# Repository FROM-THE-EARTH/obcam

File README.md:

# obcam

`obcam` is the flight camera module and program for the OB team rocket in NSE 2022. See [the site](https://FROM-THE-EARTH.github.io/obcam/) for details.

## Install

After configuration for network connection and installation of `git` and `pip`, run

```bash
python -m pip install git+https://github.com/FROM-THE-EARTH/obcam.git
```

## Install and Activate the flight camera mode

After configuration for network connection and installation of `git`, run

```bash
git clone https://github.com/FROM-THE-EARTH/obcam.git
cd obcam

# After filling out and confirming the glm.py
# See the documentation for detail of the settings.
sudo ./install.sh
```

## Scripts

Scripts in the `scripts` directory may be useful if you want some small operations like installing just `obcam`, activate the flight camera mode, or deactivate the flight camera mode. See [the site](https://FROM-THE-EARTH.github.io/obcam/scripts/) for more information.

**`install.sh`**

This script installs `obcam` and activates the flight camera mode simultaneously.

**`scripts/activate_flightcam.sh`**

This script activates the flight camera mode of the `obcam`. In the flight camera mode, the program of the `obcam` run automatically when booting.

**`scripts/deactivate_flightcam.sh`**

This script deactivates the flight camera mode.

**`scripts/expand_swap.sh`**

This script expands size of the swap file `/var/swap`. In the default setting, size of the swap will be changed to 2048 MB.

**`scripts/install_obcam.sh`**

This script installs the `obcam` module using `pip`. Note that `pip` should be installed before executing this script.

**`scripts/install_pip.sh`**

This script installs `pip`. Note that `pip` could be not installed yet right after the first booting. Thus, this script might be useful in the situation.

**`scripts/uninstall_obcam.sh`**

This script uninstalls the `obcam` module using `pip`.

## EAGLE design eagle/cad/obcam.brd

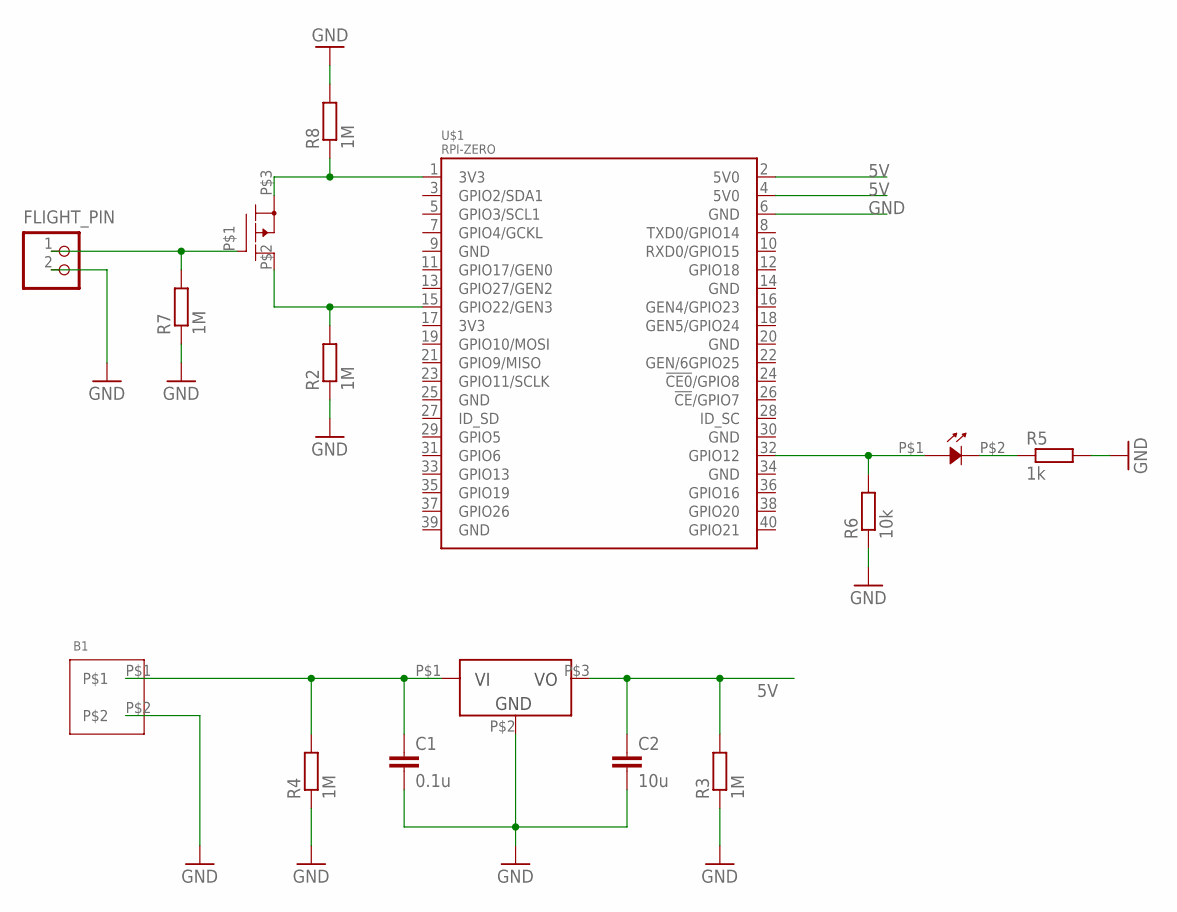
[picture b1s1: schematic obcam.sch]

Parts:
B1: 9V_BATTERY_HOLDER
C1: 0.1u; C2012
C2: 10u; C2012
D1: SML-E1X
FLIGHT_PIN: B2B-XH-A
IC1: NJM2391; TO252
IC2: TJ8S06M3L; TO252
R2, R3, R4, R7, R8: 1M; M2012
R5: 1k; M2012
R6: 10k; M2012
U$1: RPI-ZERO; RASP_PI_ZERO_BOARD_FULL

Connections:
3V3@1: IC2.P$3, R8.1, U$1.1 (3V3)
5V: C2.1, IC1.P$3, R3.2, U$1.2 (5V0), U$1.4 (5V0)
FLIGHT_IO: IC2.P$2, R2.2, U$1.15 (GPIO22/GEN3)
GND: B1.P$2, C1.2, C2.2, FLIGHT_PIN.2, IC1.P$2, R2.1, R3.1, R4.1, R5.2, R6.1, R7.1, R8.2, U$1.6 (GND)
unnamed: B1.P$1, C1.1, IC1.P$1, R4.2
unnamed: FLIGHT_PIN.1, IC2.P$1, R7.2
unnamed: D1.P$2, R5.1
unnamed: D1.P$1, R6.2, U$1.32 (GPIO12)

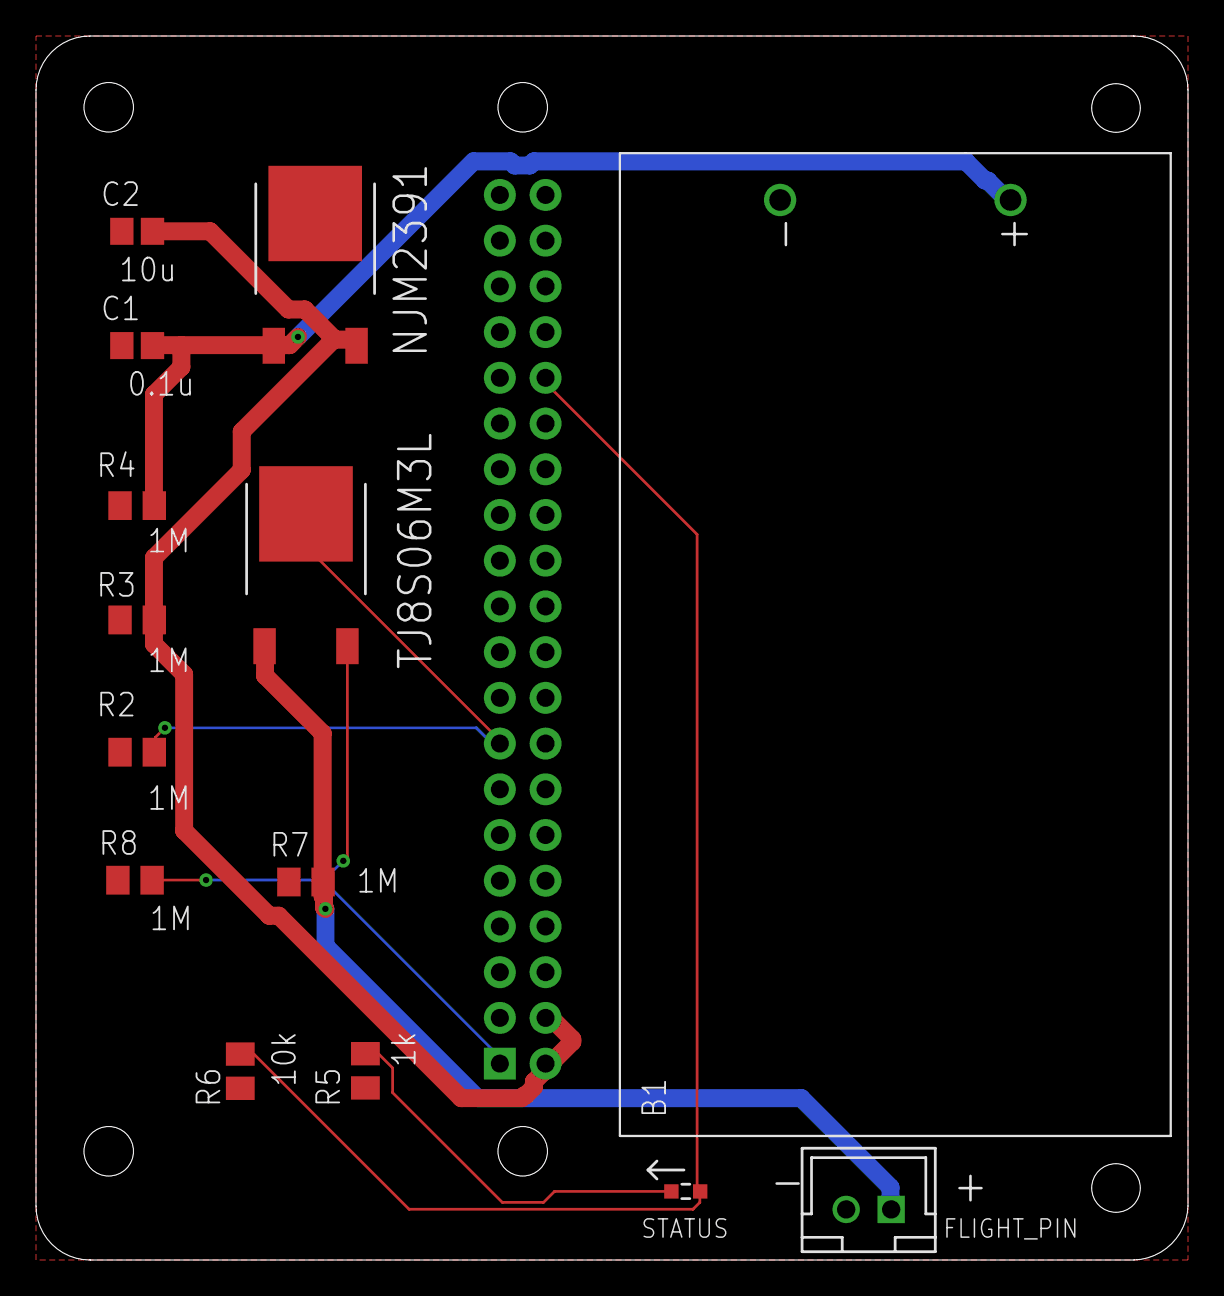
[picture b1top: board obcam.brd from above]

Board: 2 copper layers, 64.0 x 68.0 mm, 15 parts (1 on the bottom side), 8 nets.

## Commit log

2022-07-30 first commit.
2022-07-30 Added installation of `distutils` for `pip`.
2022-07-30 Added small scripts for operation.
2022-07-30 Changed modes of scripts to be executable.
2022-07-30 Added explanation of the scripts.
2022-07-30 Changed the flight pin level logic.
2022-07-30 Took noise measures when detecting a flight pin to be connected.
2022-07-30 Fixed a bug aboout noise measures.
2022-07-30 Added another command for activating camera
2022-07-30 Fixed the library of TJ8S06M3L and updated CAD.
2022-07-30 Removed an useless line for activation of camera
2022-07-31 Added a rule for YAML.
2022-07-31 Added pre-commit settings.
2022-07-31 Fixed the pre-commit settings.
2022-07-31 Wrote the documentation.
2022-07-31 Fixed typos.
2022-07-31 Added an action that updates the site of GitHub pages.
2022-07-31 Updated package dependencies.
2022-07-31 Took a measure for stop of power supply.
2022-08-01 Added new parameter `framerate`. #3
2022-08-01 Updated the default value of `resolution`. #3
2022-08-01 Updated the default value of `interval`. #3
2022-08-01 Reflected changes of setting values to the documentation. #3
2022-08-01 Added the description about maximum values of settings. #3
2022-08-01 Fixed a type. #3
2022-08-01 Added new parameter `parent_dir` to specify the parent directory of output files. #3
2022-08-01 Fixed the bug that fails format validation of video files. #3
2022-08-01 Incremented the version number.
2022-08-01 Defined a formatter and applied it. #2
2022-08-01 Changed so that the program only use the root logger. #2
2022-08-01 Added description about outputs from the application. #2
2022-08-01 Added the top image.
2022-08-01 Fixed a typo.
2022-08-02 Added verbose log outputs for debugging. #8
2022-08-02 Changed to run recording in the main thread. #8
2022-08-02 Reflected the changes about log outputs to the documentation. #8
2022-08-02 Added the process of shutting down after recording and restarting the app. #1
2022-08-02 Implemented the command that exits the program before shutting down. #1
2022-08-02 Changed the logic of waiting connection of a flight pin. #1
2022-08-03 Removed `activate_camera.sh`.
2022-08-03 Added description about enabling legacy camera support.
2022-08-03 Fixed typo.
2022-08-03 Reflected the current application flow to the flowchart.
2022-08-03 Updated description about assembly and flow of the program.
2022-08-03 Added details of output files.
2022-08-03 Added description about how to extract data from SD cards. #14
2022-08-03 Added description about how to convert video format from H264 to MP4. #14
2022-08-03 Made the checklist. #14
2022-08-03 Added the trouble shooting. #14
2022-08-03 Reflected the changes so far to README. #14
2022-08-03 Fixed the bug that causes deadlock of `lock_in_recording`.
2022-08-03 Deployed d80989c with MkDocs version: 1.3.1
2022-08-03 Added the documentation in Japanese. #18
2022-08-03 Added the script that builds the documentation. #18
2022-08-03 Updated the deploy process of the documentation. #18
2022-08-03 Fixed bug that shuts down when the command EXIT is activated.
2022-08-03 Update gh-pages to output generated at e85f07d
2022-08-03 Fixed bug that the language selector indicates invalid URLs.
2022-08-03 Update gh-pages to output generated at 4c12300
2022-08-04 Added the script that expands size of swap file. #21
2022-08-04 Added the process of expansion of a swap file. #21
2022-08-04 Reflected the changes about expansion of a swap file. #21
2022-08-04 Update gh-pages to output generated at cc13cdf
2022-08-04 Removed useless precommit scripts.
2022-08-04 Fixed invalid edit URLs.
2022-08-04 Update gh-pages to output generated at cac5258
2022-08-04 Updated the flowchart so that includes descriptions about status LED.
2022-08-04 Update gh-pages to output generated at 5fad42e
2022-08-08 Revised the code of waiting until a flight pin connected not to be CPU-bound. #24
2022-08-08 Added description about update of `obcam`.
2022-08-08 Update gh-pages to output generated at 32fcedf
2022-08-15 Fixed bug that raises `AttributeError` if camera is not detected.
2022-08-15 Enabled to catch exception whlie creating new `IORecorder`.
2022-08-15 Update gh-pages to output generated at f87a4eb
2022-08-15 Made log outputs more detail when camera connection is disabled.
2022-08-15 Update gh-pages to output generated at d0c57a5
